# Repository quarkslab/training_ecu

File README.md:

# training_ecu
Hardware and software for the ECU we use during trainings

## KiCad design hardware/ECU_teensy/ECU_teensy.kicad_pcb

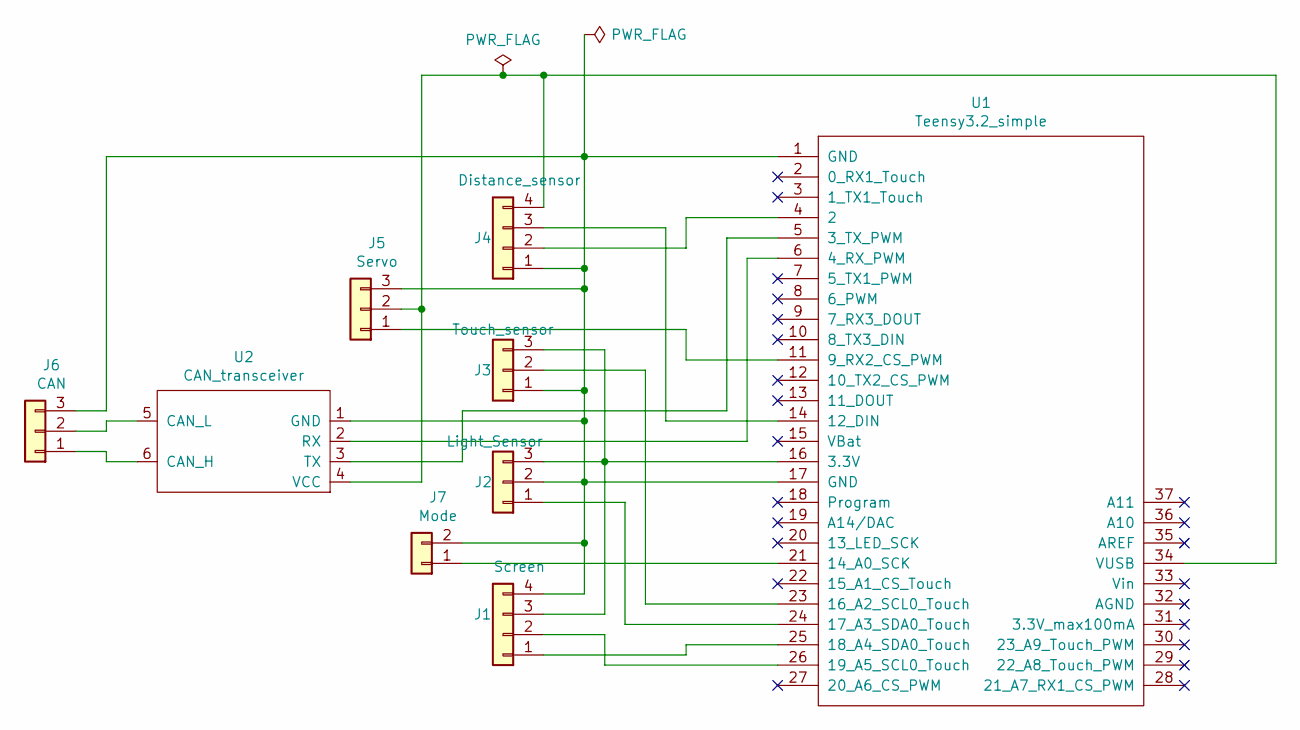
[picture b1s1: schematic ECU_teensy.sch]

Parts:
J1: Screen; PinHeader_1x04_P2.54mm_Vertical
J2: Light_Sensor; PinHeader_1x03_P2.54mm_Vertical
J3: Touch_sensor; PinHeader_1x03_P2.54mm_Vertical
J4: Distance_sensor; PinHeader_1x04_P2.54mm_Vertical
J5: Servo; PinHeader_1x03_P2.54mm_Vertical
J6: CAN; PinHeader_1x03_P2.54mm_Vertical
J7: Mode; PinHeader_1x02_P2.54mm_Vertical
U1: Teensy3.2_simple; Teensy30_31_32_LC_simple
U2: CAN_transceiver

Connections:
unnamed: J1.1, U1.25 (18_A4_SDA0_Touch)
unnamed: J1.2, U1.26 (19_A5_SCL0_Touch)
unnamed: J1.3, J2.3, J3.3, U1.16 (3.3V)
unnamed: J1.4, J2.2, J3.1, J4.1, J5.3, J6.3, J7.2, U1.1 (GND), U1.17 (GND), U2.1 (GND)
unnamed: J2.1, U1.24 (17_A3_SDA0_Touch)
unnamed: J3.2, U1.23 (16_A2_SCL0_Touch)
unnamed: J4.2, U1.4 (2)
unnamed: J4.3, U1.14 (12_DIN)
unnamed: J4.4, J5.2, U1.34 (VUSB), U2.4 (VCC)
unnamed: J5.1, U1.11 (9_RX2_CS_PWM)
unnamed: J6.1, U2.6 (CAN_H)
unnamed: J6.2, U2.5 (CAN_L)
unnamed: J7.1, U1.21 (14_A0_SCK)
unnamed: U1.5 (3_TX_PWM), U2.3 (TX)
unnamed: U1.6 (4_RX_PWM), U2.2 (RX)

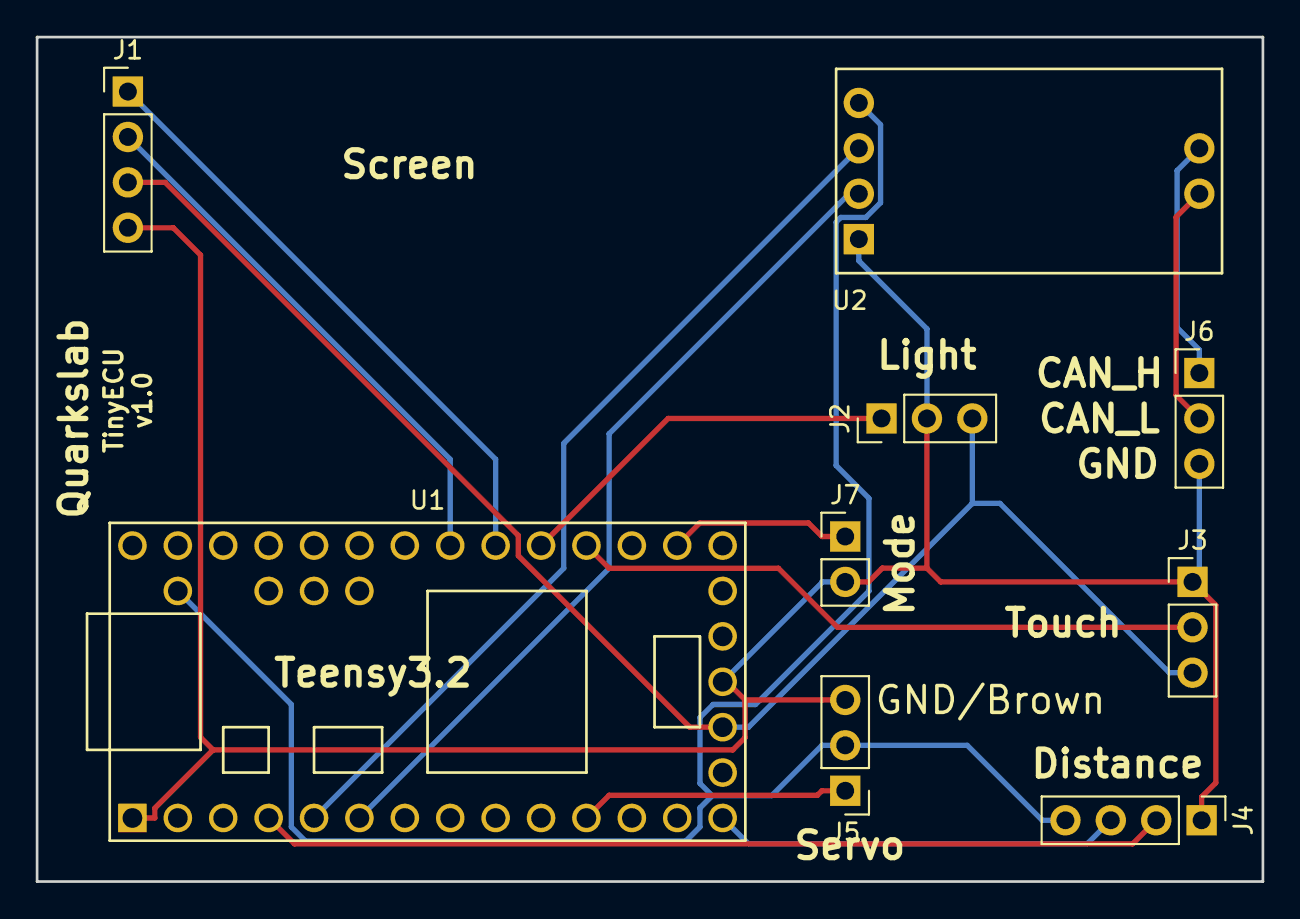
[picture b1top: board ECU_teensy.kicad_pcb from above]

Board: 2 copper layers, 68.6 x 47.2 mm, 9 parts (0 on the bottom side), 15 nets.

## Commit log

2019-04-29 First release
